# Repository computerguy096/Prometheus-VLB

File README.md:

# Prometheus VLB - an affordable way to get a fast video card for your VLB systems

This is an open source video card, designed to be used in systems with a VLB slot, like a 486 class machine. It's designed around the S3 Trio64V+ video chip (86C765), which can be found in many PCI video cards, as wel as separately.
As a bonus, this particular chip allows for a very easy implementation for the VL bus, with almost no support components required, even the RAMDAC is built into the chip.
The card was designed from scratch, using only the official datasheet and photos of an STB Powergraph 64 for a few visual references.

## Features

- S3 Trio64V+ (86C765) or S3 ViRGE (86C325)[^1] video chip, with a powerful and very compatible 2D core, perfect for most DOS games
- up to 2MB of fast page or EDO memory, with clearance for SOJ sockets
- configurable address range, with 32MB, 64MB and 1024MB as options
- simple design, built in RAMDAC, only requires a few extra parts
- fully configurable registers with pull-downs, allowing the tuning of various parameters like memory timings, etc.
- flexible EEPROM implementation, allows DIP28, DIP32, as well as PLCC32 footprints
- common VGA connector placement, allows reusability for many of the old metallic brackets
- small PCB, which does not extend below the card edge in the front, so it will not collide with keyboard controller chips on some boards

## Documentation

Trio64V+ datasheet can be read [here](docs/DB018-A_Trio64V+_Integrated_Graphics_Video_Accelerator_Jul95.pdf), and the ViRGE datasheet [here](docs/DB019-B_ViRGE_Integrated_3D_Accelerator_Aug1996.pdf).

## FAQ

**Q: Is this for sale? Where can I buy one?**

> Nope, it's not for sale, and I do not have any intentions to sell them. However, I am an advocate for open source hardware so the design is fully public (the gerbers, the schematic, everything, all provided under GPLv3) so you can build your own card freely.

**Q: What parts do I need to build a card?**

> There is a [CSV BOM](kicad/virge-vlb.csv) included, as well as an [interactive HTML BOM](kicad/bom/ibom.html), with all the parts and their quantities listed. The main thing to acquire is the S3 chip itself, which can be salvaged from PCI cards or bought as NOS trays. 
**Be careful with the chip model, only 86C765 and 86C325 are fully pin compatible and will work!**

**Q: What about the video BIOS?**

> The binary is from an STB Powergraph64 (closest card to this one in terms of design) and it is available in the repository right [here](VBIOS.BIN)

**Q: Where can i find the gerber files?**

> At `/kicad/gerber` on this repo.

## Footnotes

[^1]: S3 ViRGE support is experimental in VLB mode, since there are no drivers available for it.

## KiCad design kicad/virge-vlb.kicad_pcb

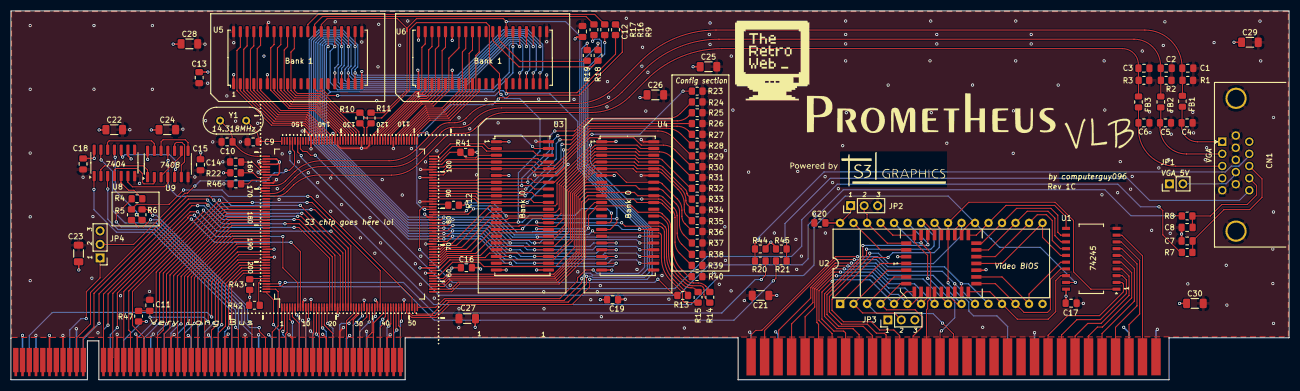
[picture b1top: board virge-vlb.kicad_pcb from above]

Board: 4 copper layers, 240.5 x 69.4 mm, 96 parts (0 on the bottom side), 241 nets.

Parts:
C1, C2, C3, C4, C5, C6, C7, C8, C9, C10: 10pF; C_0805_2012Metric_Pad1.18x1.45mm_HandSolder
C11: 100pF; C_0805_2012Metric_Pad1.18x1.45mm_HandSolder
C12, C13, C14, C15, C16, C17, C18, C19, C20: 100nF; C_0805_2012Metric_Pad1.18x1.45mm_HandSolder
C21, C22, C23, C24, C25, C26, C27, C28, C29, C30: 10uF; C_1206_3216Metric_Pad1.33x1.80mm_HandSolder
CN1: VGA; DSUB-15_female
FB1, FB2, FB3: FerriteBead; L_0805_2012Metric_Pad1.15x1.40mm_HandSolder
J1: VLB_slot; BUS_VLB_Board
JP1: Conn_01x02; PinHeader_1x02_P2.54mm_Vertical
JP2, JP3, JP4: Conn_01x03; PinHeader_1x03_P2.54mm_Vertical
R1, R2, R3: 75R; R_0805_2012Metric_Pad1.20x1.40mm_HandSolder
R4, R5, R6: 0R; R_0805_2012Metric_Pad1.20x1.40mm_HandSolder
R7, R8, R9, R10, R11, R12, R13, R14, R15, R16, R17, R18, R19, R20, R21: 33R; R_0805_2012Metric_Pad1.20x1.40mm_HandSolder
R22, R23, R24, R25, R26, R27, R28, R29, R30, R31, R32, R33, R34, R35, R36, R37, R38, R39, R40, R41, R42, R43, R44, R45: 10K; R_0805_2012Metric_Pad1.20x1.40mm_HandSolder
R46, R47: 150R; R_0805_2012Metric_Pad1.20x1.40mm_HandSolder
U1: 74LS245; SO-20_12.8x7.5mm_P1.27mm
U2: 27C020; EEPROM_combo
U3, U4, U5, U6: V53C16258H; SOJ-40_10.16x26.00mm_P1.27mm
U7: 86C765; QFP-208
U8: 7404; SO-14_3.9x8.65mm_P1.27mm
U9: 7408; SO-14_3.9x8.65mm_P1.27mm
Y1: 14.318MHz; Crystal_HC18-U_Vertical

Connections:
/BLUE: C6.1, CN1.3, FB3.1
/DDC_SCL: R21.1, U7.205 (SPCLK/ESYNC)
/DDC_SDA: R20.1, U7.206 (SPD/~BLANK)
/GREEN: C5.1, CN1.2, FB2.1
/HS: R7.1, U7.149 (HSYNC)
/HS_VGA: C7.1, CN1.13, R7.2
/ISA Bus/ISA_D0: J1.C40 (DB0), U1.2 (A0)
/ISA Bus/ISA_D1: J1.C39 (DB1), U1.3 (A1)
/ISA Bus/ISA_D2: J1.C38 (DB2), U1.4 (A2)
/ISA Bus/ISA_D3: J1.C37 (DB3), U1.5 (A3)
/ISA Bus/ISA_D4: J1.C36 (DB4), U1.6 (A4)
/ISA Bus/ISA_D5: J1.C35 (DB5), U1.7 (A5)
/ISA Bus/ISA_D6: J1.C34 (DB6), U1.8 (A6)
/ISA Bus/ISA_D7: J1.C33 (DB7), U1.9 (A7)
/ISA Bus/R_A0: J1.C62 (BA00), U2.12 (A0)
/ISA Bus/R_A1: J1.C61 (BA01), U2.11 (A1)
/ISA Bus/R_A2: J1.C60 (BA02), U2.10 (A2)
/ISA Bus/R_A3: J1.C59 (BA03), U2.9 (A3)
/ISA Bus/R_A4: J1.C58 (BA04), U2.8 (A4)
/ISA Bus/R_A5: J1.C57 (BA05), U2.7 (A5)
/ISA Bus/R_A6: J1.C56 (BA06), U2.6 (A6)
/ISA Bus/R_A7: J1.C55 (BA07), U2.5 (A7)
/ISA Bus/R_A8: J1.C54 (BA08), U2.27 (A8)
/ISA Bus/R_A9: J1.C53 (BA09), U2.26 (A9)
/ISA Bus/R_A10: J1.C52 (BA10), U2.23 (A10)
/ISA Bus/R_A11: J1.C51 (BA11), U2.25 (A11)
/ISA Bus/R_A12: J1.C50 (BA12), U2.4 (A12)
/ISA Bus/R_A13: J1.C49 (BA13), U2.28 (A13)
/ISA Bus/R_A14: J1.C48 (BA14), U2.29 (A14)
/ISA Bus/R_A15: J1.C47 (BA15), U2.3 (A15)
/ISA Bus/R_D0: U1.18 (B0), U2.13 (D0)
/ISA Bus/R_D1: U1.17 (B1), U2.14 (D1)
/ISA Bus/R_D2: U1.16 (B2), U2.15 (D2)
/ISA Bus/R_D3: U1.15 (B3), U2.17 (D3)
/ISA Bus/R_D4: U1.14 (B4), U2.18 (D4)
/ISA Bus/R_D5: U1.13 (B5), U2.19 (D5)
/ISA Bus/R_D6: U1.12 (B6), U2.20 (D6)
/ISA Bus/R_D7: U1.11 (B7), U2.21 (D7)
/ISA Bus/SMEMR: J1.C12 (~SMEMR), U1.1 (A->B), U2.24 (~OE)
/Memory Bus/CAS0: R12.2, U3.29 (~LCAS)
/Memory Bus/CAS1: R13.2, U3.28 (~UCAS)
/Memory Bus/CAS2: R14.2, U4.29 (~LCAS)
/Memory Bus/CAS3: R15.2, U4.28 (~UCAS)
/Memory Bus/CAS4: R16.2, U5.29 (~LCAS)
/Memory Bus/CAS5: R17.2, U5.28 (~UCAS)
/Memory Bus/CAS6: R18.2, U6.29 (~LCAS)
/Memory Bus/CAS7: R19.2, U6.28 (~UCAS)
/Memory Bus/MA0: U3.16 (A0), U4.16 (A0), U5.16 (A0), U6.16 (A0), U7.79 (MA0)
/Memory Bus/MA1: U3.17 (A1), U4.17 (A1), U5.17 (A1), U6.17 (A1), U7.77 (MA1)
/Memory Bus/MA2: U3.18 (A2), U4.18 (A2), U5.18 (A2), U6.18 (A2), U7.75 (MA2)
/Memory Bus/MA3: U3.19 (A3), U4.19 (A3), U5.19 (A3), U6.19 (A3), U7.73 (MA3)
/Memory Bus/MA4: U3.22 (A4), U4.22 (A4), U5.22 (A4), U6.22 (A4), U7.72 (MA4)
/Memory Bus/MA5: U3.23 (A5), U4.23 (A5), U5.23 (A5), U6.23 (A5), U7.74 (MA5)
/Memory Bus/MA6: U3.24 (A6), U4.24 (A6), U5.24 (A6), U6.24 (A6), U7.76 (MA6)
/Memory Bus/MA7: U3.25 (A7), U4.25 (A7), U5.25 (A7), U6.25 (A7), U7.78 (MA7)
/Memory Bus/MA8: U3.26 (A8), U4.26 (A8), U5.26 (A8), U6.26 (A8), U7.80 (MA8)
/Memory Bus/OE: R11.2, U3.27 (OE), U4.27 (OE), U5.27 (OE), U6.27 (OE)
/Memory Bus/PD0: U3.2 (DQ0), U7.104 (PD0)
/Memory Bus/PD1: R41.2, U3.3 (DQ1), U7.102 (PD1)
/Memory Bus/PD2: R29.2, U3.4 (DQ2), U7.100 (PD2)
/Memory Bus/PD3: R30.2, U3.5 (DQ3), U7.97 (PD3)
/Memory Bus/PD4: R25.2, U3.7 (DQ4), U7.94 (PD4)
/Memory Bus/PD5: R26.2, U3.8 (DQ5), U7.92 (PD5)
/Memory Bus/PD6: R27.2, U3.9 (DQ6), U7.90 (PD6)
/Memory Bus/PD7: R28.2, U3.10 (DQ7), U7.88 (PD7)
/Memory Bus/PD8: U3.31 (DQ8), U7.89 (PD8)
/Memory Bus/PD9: U3.32 (DQ9), U7.91 (PD9)
/Memory Bus/PD10: R24.2, U3.33 (DQ10), U7.93 (PD10)
/Memory Bus/PD11: R39.2, U3.34 (DQ11), U7.95 (PD11)
/Memory Bus/PD12: R23.2, U3.36 (DQ12), U7.98 (PD12)
/Memory Bus/PD13: U3.37 (DQ13), U7.101 (PD13)
/Memory Bus/PD14: U3.38 (DQ14), U7.103 (PD14)
/Memory Bus/PD15: U3.39 (DQ15), U7.105 (PD15)
/Memory Bus/PD16: R31.2, U4.2 (DQ0), U7.69 (PD16)
/Memory Bus/PD17: R32.2, U4.3 (DQ1), U7.67 (PD17)
/Memory Bus/PD18: R33.2, U4.4 (DQ2), U7.65 (PD18)
/Memory Bus/PD19: R35.2, U4.5 (DQ3), U7.63 (PD19)
/Memory Bus/PD20: U4.7 (DQ4), U7.59 (PD20)
/Memory Bus/PD21: U4.8 (DQ5), U7.57 (PD21)
/Memory Bus/PD22: U4.9 (DQ6), U7.55 (PD22)
/Memory Bus/PD23: U4.10 (DQ7), U7.53 (PD23)
/Memory Bus/PD24: R40.2, U4.31 (DQ8), U7.54 (PD24)
/Memory Bus/PD25: R38.2, U4.32 (DQ9), U7.56 (PD25)
/Memory Bus/PD26: R37.2, U4.33 (DQ10), U7.58 (PD26)
/Memory Bus/PD27: R36.2, U4.34 (DQ11), U7.61 (PD27)
/Memory Bus/PD28: R34.2, U4.36 (DQ12), U7.64 (PD28)
/Memory Bus/PD29: U4.37 (DQ13), U7.66 (PD29)
/Memory Bus/PD30: U4.38 (DQ14), U7.68 (PD30)
/Memory Bus/PD31: U4.39 (DQ15), U7.70 (PD31)
/Memory Bus/PD32: U5.2 (DQ0), U7.143 (PD32)
/Memory Bus/PD33: U5.3 (DQ1), U7.141 (PD33)
/Memory Bus/PD34: U5.4 (DQ2), U7.139 (PD34)
/Memory Bus/PD35: U5.5 (DQ3), U7.136 (PD35)
/Memory Bus/PD36: U5.7 (DQ4), U7.133 (PD36)
/Memory Bus/PD37: U5.8 (DQ5), U7.131 (PD37)
/Memory Bus/PD38: U5.9 (DQ6), U7.129 (PD38)
/Memory Bus/PD39: U5.10 (DQ7), U7.127 (PD39)
/Memory Bus/PD40: U5.31 (DQ8), U7.128 (PD40)
/Memory Bus/PD41: U5.32 (DQ9), U7.130 (PD41)
/Memory Bus/PD42: U5.33 (DQ10), U7.132 (PD42)
/Memory Bus/PD43: U5.34 (DQ11), U7.134 (PD43)
/Memory Bus/PD44: U5.36 (DQ12), U7.138 (PD44)
/Memory Bus/PD45: U5.37 (DQ13), U7.140 (PD45)
/Memory Bus/PD46: U5.38 (DQ14), U7.142 (PD46)
/Memory Bus/PD47: U5.39 (DQ15), U7.144 (PD47)
/Memory Bus/PD48: U6.2 (DQ0), U7.121 (PD48)
/Memory Bus/PD49: U6.3 (DQ1), U7.119 (PD49)
/Memory Bus/PD50: U6.4 (DQ2), U7.117 (PD50)
/Memory Bus/PD51: U6.5 (DQ3), U7.115 (PD51)
/Memory Bus/PD52: U6.7 (DQ4), U7.112 (PD52)
/Memory Bus/PD53: U6.8 (DQ5), U7.110 (PD53)
/Memory Bus/PD54: U6.9 (DQ6), U7.108 (PD54)
/Memory Bus/PD55: U6.10 (DQ7), U7.106 (VCLKI/PD55)
/Memory Bus/PD56: U6.31 (DQ8), U7.107 (PD56)
/Memory Bus/PD57: U6.32 (DQ9), U7.109 (PD57)
/Memory Bus/PD58: U6.33 (DQ10), U7.111 (PD58)
/Memory Bus/PD59: U6.34 (DQ11), U7.113 (PD59)
/Memory Bus/PD60: U6.36 (DQ12), U7.116 (PD60)
/Memory Bus/PD61: U6.37 (DQ13), U7.118 (PD61)
/Memory Bus/PD62: U6.38 (DQ14), U7.120 (PD62)
/Memory Bus/PD63: U6.39 (DQ15), U7.122 (PD63)
/Memory Bus/RAS: R9.2, U3.14 (~RAS), U4.14 (~RAS), U5.14 (~RAS), U6.14 (~RAS)
/Memory Bus/WE: R10.2, U3.13 (~WE), U4.13 (~WE), U5.13 (~WE), U6.13 (~WE)
/RED: C4.1, CN1.1, FB1.1
/S3_BLUE: C3.1, FB3.2, R3.1, U7.172 (AB)
/S3_GREEN: C2.1, FB2.2, R2.1, U7.171 (AG)
/S3_RED: C1.1, FB1.2, R1.1, U7.168 (AR)
/VL Bus/ADS: J1.A45 (ADS), U7.20 (~SADS)
/VL Bus/BE0: J1.A39 (BE0), U7.38 (~SBE0)
/VL Bus/BE1: J1.A41 (BE1), U7.27 (~SBE1)
/VL Bus/BE2: J1.A42 (BE2), U7.19 (~SBE2)
/VL Bus/BE3: J1.A44 (BE3), U7.7 (~SBE3)
/VL Bus/IRQ9: J1.B50 (IRQ9), JP4.1
/VL Bus/LCLK: J1.B56 (LCLK), U7.194 (SCLK)
/VL Bus/LDEV: J1.A49 (LDEV), U7.24 (~LOCA)
/VL Bus/LRDY: J1.A48 (LRDY), U7.23 (~SRDY)
/VL Bus/M/IO: J1.B44 (M/IO), U7.8 (SM/~IO)
/VL Bus/RDYR: J1.B48 (RDYRTN), U7.21 (~RDYIN)
/VL Bus/RST: J1.B42 (~RESET), R47.2
/VL Bus/SAUP1: U7.25 (SAUP1), U9.11
/VL Bus/SAUP2: R5.2, U7.50 (SAUP2)
/VL Bus/VL_A2: J1.B40 (A2), U7.176 (SA2)
/VL Bus/VL_A3: J1.B39 (A3), U7.177 (SA3)
/VL Bus/VL_A4: J1.A37 (A4), U7.178 (SA4)
/VL Bus/VL_A5: J1.B37 (A5), U7.179 (SA5)
/VL Bus/VL_A6: J1.A36 (A6), U7.180 (SA6)
/VL Bus/VL_A7: J1.B36 (A7), U7.181 (SA7)
/VL Bus/VL_A8: J1.A34 (A8), U7.182 (SA8)
/VL Bus/VL_A9: J1.B35 (A9), U7.183 (SA9)
/VL Bus/VL_A10: J1.A33 (A10), U7.185 (SA10)
/VL Bus/VL_A11: J1.B34 (A11), U7.186 (SA11)
/VL Bus/VL_A12: J1.A32 (A12), U7.187 (SA12)
/VL Bus/VL_A13: J1.B33 (A13), U7.188 (SA13)
/VL Bus/VL_A14: J1.A31 (A14), U7.189 (SA14)
/VL Bus/VL_A15: J1.B31 (A15), U7.190 (SA15)
/VL Bus/VL_A16: J1.A30 (A16), U7.191 (SA16)
/VL Bus/VL_A17: J1.B30 (A17), U7.196 (SA17)
/VL Bus/VL_A18: J1.A29 (A18), U7.197 (SA18)
/VL Bus/VL_A19: J1.B28 (A19), U7.198 (SA19)
/VL Bus/VL_A20: J1.A28 (A20), U7.199 (SA20)
/VL Bus/VL_A21: J1.B27 (A21), U7.200 (SA21)
/VL Bus/VL_A22: J1.A26 (A22), U7.201 (SA22)
/VL Bus/VL_A23: J1.B26 (A23), U8.1
/VL Bus/VL_A23+A24: U9.3, U9.9
/VL Bus/VL_A23-A26: U9.8, U9.12
/VL Bus/VL_A23_O: U8.2, U9.1
/VL Bus/VL_A24: J1.A25 (A24), U8.3
/VL Bus/VL_A24_O: U8.4, U9.2
/VL Bus/VL_A25: J1.B25 (A25), R4.2
/VL Bus/VL_A25+A26: U9.6, U9.10
/VL Bus/VL_A25_O: U8.6, U9.4
/VL Bus/VL_A26: J1.A23 (A26), R6.2
/VL Bus/VL_A26_O: U8.10, U9.5
/VL Bus/VL_A29: J1.B23 (A29), U8.13
/VL Bus/VL_A29_O: U8.12, U9.13
/VL Bus/VL_A30: J1.A21 (A30), R5.1
/VL Bus/VL_D0: J1.B1 (D0), U7.46 (SD0)
/VL Bus/VL_D1: J1.A1 (D1), U7.45 (SD1)
/VL Bus/VL_D2: J1.B2 (D2), U7.44 (SD2)
/VL Bus/VL_D3: J1.A2 (D3), U7.43 (SD3)
/VL Bus/VL_D4: J1.B3 (D4), U7.42 (SD4)
/VL Bus/VL_D5: J1.A4 (D5), U7.41 (SD5)
/VL Bus/VL_D6: J1.B4 (D6), U7.40 (SD6)
/VL Bus/VL_D7: J1.A5 (D7), U7.39 (SD7)
/VL Bus/VL_D8: J1.B5 (D8), U7.36 (SD8)
/VL Bus/VL_D9: J1.A6 (D9), U7.35 (SD9)
/VL Bus/VL_D10: J1.B7 (D10), U7.34 (SD10)
/VL Bus/VL_D11: J1.A7 (D11), U7.33 (SD11)
/VL Bus/VL_D12: J1.B8 (D12), U7.31 (SD12)
/VL Bus/VL_D13: J1.A8 (D13), U7.30 (SD13)
/VL Bus/VL_D14: J1.B10 (D14), U7.29 (SD14)
/VL Bus/VL_D15: J1.A9 (D15), U7.28 (SD15)
/VL Bus/VL_D16: J1.B11 (D16), U7.18 (SD16)
/VL Bus/VL_D17: J1.A11 (D17), U7.17 (SD17)
/VL Bus/VL_D18: J1.B12 (D18), U7.16 (SD18)
/VL Bus/VL_D19: J1.A13 (D19), U7.15 (SD19)
/VL Bus/VL_D20: J1.B13 (D20), U7.14 (SD20)
/VL Bus/VL_D21: J1.A14 (D21), U7.13 (SD21)
/VL Bus/VL_D22: J1.B15 (D22), U7.11 (SD22)
/VL Bus/VL_D23: J1.A15 (D23), U7.10 (SD23)
/VL Bus/VL_D24: J1.B16 (D24), U7.6 (SD24)
/VL Bus/VL_D25: J1.A16 (D25), U7.5 (SD25)
/VL Bus/VL_D26: J1.B17 (D26), U7.4 (SD26)
/VL Bus/VL_D27: J1.A18 (D27), U7.3 (SD27)
/VL Bus/VL_D28: J1.B18 (D28), U7.2 (SD28)
/VL Bus/VL_D29: J1.A19 (D29), U7.1 (SD29)
/VL Bus/VL_D30: J1.B19 (D30), U7.208 (SD30)
/VL Bus/VL_D31: J1.A20 (D31), U7.207 (SD31)
/VL Bus/W/R: J1.B45 (W/R), U7.26 (SW/~R)
/VS: R8.1, U7.150 (VSYNC)
/VS_VGA: C8.1, CN1.14, R8.2
GND: C1.2, C2.2, C3.2, C4.2, C5.2, C6.2, C7.2, C8.2, C9.1, C10.1, C11.2, C12.1, C13.2, C14.2, C15.2, C16.2, C17.2, C18.2, C19.2, C20.1, C21.2, C22.2, C23.2, C24.2, C25.2, C26.2, C27.2, C28.2, C29.2, C30.2, CN1.5, CN1.6, CN1.7, CN1.8, CN1.10, J1.A3 (VSS), J1.A10 (VSS), J1.A17 (VSS), J1.A24 (VSS), J1.A35 (VSS), J1.A43 (VSS), J1.A51 (VSS), J1.B6 (VSS), J1.B14 (VSS), J1.B22 (VSS), J1.B29 (VSS), J1.B38 (VSS), J1.B49 (VSS), J1.B55 (VSS), J1.C1 (GND), J1.C10 (GND), J1.C31 (GND), JP2.3, JP3.3, R1.2, R2.2, R3.2, R23.1, R24.1, R25.1, R26.1, R27.1, R28.1, R29.1, R30.1, R31.1, R32.1, R33.1, R34.1, R35.1, R36.1, R37.1, R38.1, R39.1, R40.1, R41.1, R46.1, U1.10 (GND), U2.16 (GND), U3.21 (VSS), U3.35 (VSS), U3.40 (VSS), U4.21 (VSS), U4.35 (VSS), U4.40 (VSS), U5.21 (VSS), U5.35 (VSS), U5.40 (VSS), U6.21 (VSS), U6.35 (VSS), U6.40 (VSS), U7.9 (VSS), U7.22 (VSS), U7.32 (VSS), U7.47 (VSS), U7.60 (VSS), U7.71 (VSS), U7.87 (VSS), U7.99 (VSS), U7.114 (VSS), U7.123 (VSS), U7.126 (VSS), U7.135 (VSS), U7.145 (VSS), U7.159 (AVSS), U7.161 (AVSS), U7.163 (AVSS), U7.167 (AVSS), U7.173 (AVSS), U7.195 (VSS), U8.7 (GND), U9.7 (GND)
unnamed: CN1.12, R20.2, R44.2
unnamed: CN1.15, R21.2, R45.2
unnamed: CN1.9, JP1.2
unnamed: JP2.2, U2.30 (A17)
unnamed: JP3.2, U2.2 (A16)
unnamed: JP4.2, U7.152 (SINTR)
unnamed: R4.1, U8.5
unnamed: R6.1, U8.11
unnamed: R12.1, U7.86 (~CAS0)
unnamed: R13.1, U7.85 (~CAS1)
unnamed: R14.1, U7.83 (~CAS2)
unnamed: R15.1, U7.82 (~CAS3)
unnamed: R16.1, U7.48 (~CAS4)
unnamed: R17.1, U7.49 (~CAS5)
unnamed: R18.1, U7.51 (~CAS6)
unnamed: R19.1, U7.52 (~CAS7)
unnamed: R11.1, U7.124 (~OE)
unnamed: R9.1, U7.84 (~RAS0)
unnamed: R10.1, U7.125 (~WE)
unnamed: C11.1, R47.1, U7.193 (~SRESET)
unnamed: R46.2, U7.166 (RSET)
unnamed: C14.1, U7.162 (VREF)
unnamed: C9.2, U7.156 (XIN), Y1.2
unnamed: C10.2, U7.157 (XOUT), Y1.1
unnamed: R42.1, U7.204 (~CREQ/CRDY/EVCLK)
unnamed: R22.1, U7.165 (~PDOWN)
unnamed: R43.1, U7.203 (~VREQ/VRDY/EVIDEO)
ROMCS: U1.19 (CE), U2.22 (~CE), U7.153 (~ROMCS/GOP1)
VCC: C12.2, C13.1, C15.1, C16.1, C17.1, C18.1, C19.1, C20.2, C21.1, C22.1, C23.1, C24.1, C25.1, C26.1, C27.1, C28.1, C29.1, C30.1, J1.A12 (VCC), J1.A27 (VCC), J1.A40 (VCC), J1.A53 (VCC), J1.B9 (VCC), J1.B20 (VCC), J1.B32 (VCC), J1.B57 (VCC), J1.C3 (VCC), J1.C29 (VCC), JP1.1, JP2.1, JP3.1, R22.2, R42.2, R43.2, R44.1, R45.1, U1.20 (VCC), U2.32 (VCC), U3.1 (VCC), U3.6 (VCC), U3.20 (VCC), U4.1 (VCC), U4.6 (VCC), U4.20 (VCC), U5.1 (VCC), U5.6 (VCC), U5.20 (VCC), U6.1 (VCC), U6.6 (VCC), U6.20 (VCC), U7.12 (VDD), U7.37 (VDD), U7.62 (VDD), U7.81 (VDD), U7.96 (VDD), U7.137 (VDD), U7.158 (CLKAVDD1), U7.160 (CLKAVDD2), U7.164 (AVDD), U7.169 (AVDD), U7.170 (AVDD), U7.192 (VDD), U8.9, U8.14 (VCC), U9.14 (VCC)

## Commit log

2023-06-06 added files
2023-06-06 new readme
2023-06-06 added docs
2023-06-06 work on the memory bus, fixed symbols
2023-06-07 changed memory chips, more progress
2023-06-08 PCB work
2023-06-09 even more PCB work
2023-06-09 added VREF R for fine tuning
2023-06-09 added register strap resistors
2023-06-10 initial PCB routed
2023-06-30 added SAUP decoding, adjusted VGA conn.
2023-07-04 added ground vias, polished silkscreen
2023-07-04 added address jumpers
2023-07-05 final touches
2023-07-06 Board review changes 2023-07-06
2023-07-06 fixed some clearance issues, fixed S3 logo, fixed annotations
2023-07-13 final changes for revision 1A
2023-07-25 critical fixes for rev 1B
2023-12-04 changed QFP and ROM footprint
2023-12-05 added pull up for VREQ
2023-12-05 some polishing
2023-12-05 apparently its case sensitive
2023-12-05 yep, it was case sensitive, d'oh
2023-12-07 more readme stuff
2023-12-08 some improvements here and there
2023-12-08 cleanup
2023-12-08 more cleanup
2023-12-11 added vbios
2023-12-11 added photo
2023-12-14 some optimizations and silkscreen updating
2023-12-15 some tweaks
2023-12-15 some final tweaks
2023-12-15 updated image
2023-12-15 typo fix
2023-12-21 rounded traces + teardrops
2023-12-25 added pull up, new BOM
2023-12-25 updated bom and gerber
2024-04-06 many fixes for rev 1C
2024-04-06 updated VLB footprint
2024-04-06 fixed VGA footprint
2024-04-06 archived 1B gerber
2024-04-06 enlarged SOJ pads
2024-04-06 final fixes
2024-04-06 polishing
2024-04-07 added gerbers and teardrops, trace optimizations
2024-04-07 added 3D models, updated image
2024-04-13 fix for LS245 bus conflict
2025-03-18 updated to kicad 9
2026-03-23 small improvements

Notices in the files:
parts and their libraries:
License: 86C765 VL Bus
Licensed under the TAPR Open Hardware License (www.tapr.org/OHL)
